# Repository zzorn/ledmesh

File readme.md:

Ledmesh
=======

Overview
--------

Mesh networked nodes controlling LED light strips, LED spotlights, sensors, and other things.

The network uses wireless radio modules to communicate between nodes.

Ledmesh can be used to create coherent led lighting effects in a space (e.g. light waves flowing around walls), 
as well as for controlling 12V lighting (e.g. led spotlights).

Ledmesh can also be used as an information radiator, connecting some nodes up to computers or suitable sensors, 
and sending out light waves to nearby nodes or doing light effect changes for the whole network on different events.

Ledmesh needs configuration after installation, to tell nodes their relative locations, sensors to use for activating different modes or sending waves, and so on.

Effects
-------

The main type of effect consist of nodes sending waves of light and color along light strips towards neighboring nodes, where the waves can carry on to other nodes.
Waves can have various intensity, hue/sat/lum (also negative), wavelength, travel distance/time, random noise, color gradients, and so on.  Multiple waves can travel along a strip in various directions
at the same time, the different waves are blended together.

Waves could leave the leds at zero after they pass, or they could leave them at some other intensity, which will be changed by the next wave.  (Or the base intensity might be based on the mode(s) the node is in?)

Waves can be used to create a lot of different effects (even global fade ins or outs).  If there are some ideas for effect types that are not possible to do with waves, those might be added later.

Single outputs, like led spotlights, could be treated like a led strip of length one (or some other length, if the spotlights are arranged in a row).

Node States
-----------

Nodes can have various states depending on their sensor readings and global or remote sensor readings received with communication from other nodes.
The state(s) a node is in determines what kind of effects it generates to attached led strips and other outputs.

A node need not be either in a state or not, it can also be partially in a state (e.g. a potentiometer could be used to place a node partially in a 'lit' state).

The degree a state is activated depends either directly or indirectly on one or more sensor inputs, with some multipliers.

Different states can also have different speeds or required activation that they activate or deactivate with (a kind of inertia), to provide some hysteresis and reduce quick flickering between states.

For more complicated behaviour, the activation degree of states in the current or neighboring nodes could be used as a sensor value to help determine the activation of a node (creating a neuron-like setup).

Modes
-----

Sometimes the general apperance of the whole network should be changed.  This could be done with a mode concept, where a mode enables states contained in it, and disables states contained within any previously active mode.
Some states might be independent of the mode.

One possibility is to allow multiple modes as once, although that might be more complications than necessary.

Modes could maybe change depending on signals (which would indicate some hierarchial state system might be better than a separate mode concept).

For example, during the evening a more orange toned lighting mode could be activated, there could be modes for work that needs a lot of light, for more muted lighting for general hanging around,
for some darker and slower night illumination, a party mode, and a few different looking general light modes.

Node types
----------

There are two different types of nodes:

* Led Node
  * Controls zero or more LED strips, LED lights, etc.  Also has two extra I/O pins.
  * Has locations for sensor modules such as PIR (motion detector) and sound.
  * Has builtin light level sensor.
  * Has location for a radio communication module.

* Remote Controller
  * Contains a character LCD screen and turn wheels (and possibly a color / color gradient preview LED) for configuring the network.  It allows:
     * Configuring the length of led strips connected to different nodes (needs to be done once after installation).  
     * Defining fixed signals for different nodes (e.g. height above floor, or x/y coordinate), which can be used in effects.
     * Defining the signals that different inputs on different nodes affect, and whether the signals are global or local to the node.
       Some inputs are pre-configured (e.g. light level sensors, etc), while others could be custom (e.g. door open microswitch, red alert/instant party button, etc).
     * Defining gradients.
     * Defining various named wave types.
     * Defining various wave generators (?).
     * Defining various node states
        * Connecting wave generators to the node state
        * Specifying the activation or deactivation effects of different signals (and state activations) from this node or neighboring nodes or global signals on this state.
        * Default lifetime of this state
        * Slowness / quickness of state change = change inertia
        * Whether this state should be available on all nodes, or only a selected subset (always non-active on other nodes)  [Is this needed?  Maybe not]
     * The default screen allows setting various selected global signals, and selecting the current mode(s).
  * Could also have a USB connection to computer, and some serial based protocol to provide updates to signal states, as well as communicate states from the Ledmess network.  The protocol could also contain commands for configuring LedMesh.
  * Might also contain support for bluetooth control (for control from android app)
  * Might support an ethernet connector as well.

Control and configuration application
-------------------------------------

To be written in Java, as that allows easy porting to both android and PC.

The software on the remote controller will probably be more limited, but it would be nice to be able to do all configuration from it if needed.

Builtin Signals
---------------

* Time of day
* Age of this state (0 = newborn, 100% = at the lifetime of the state).

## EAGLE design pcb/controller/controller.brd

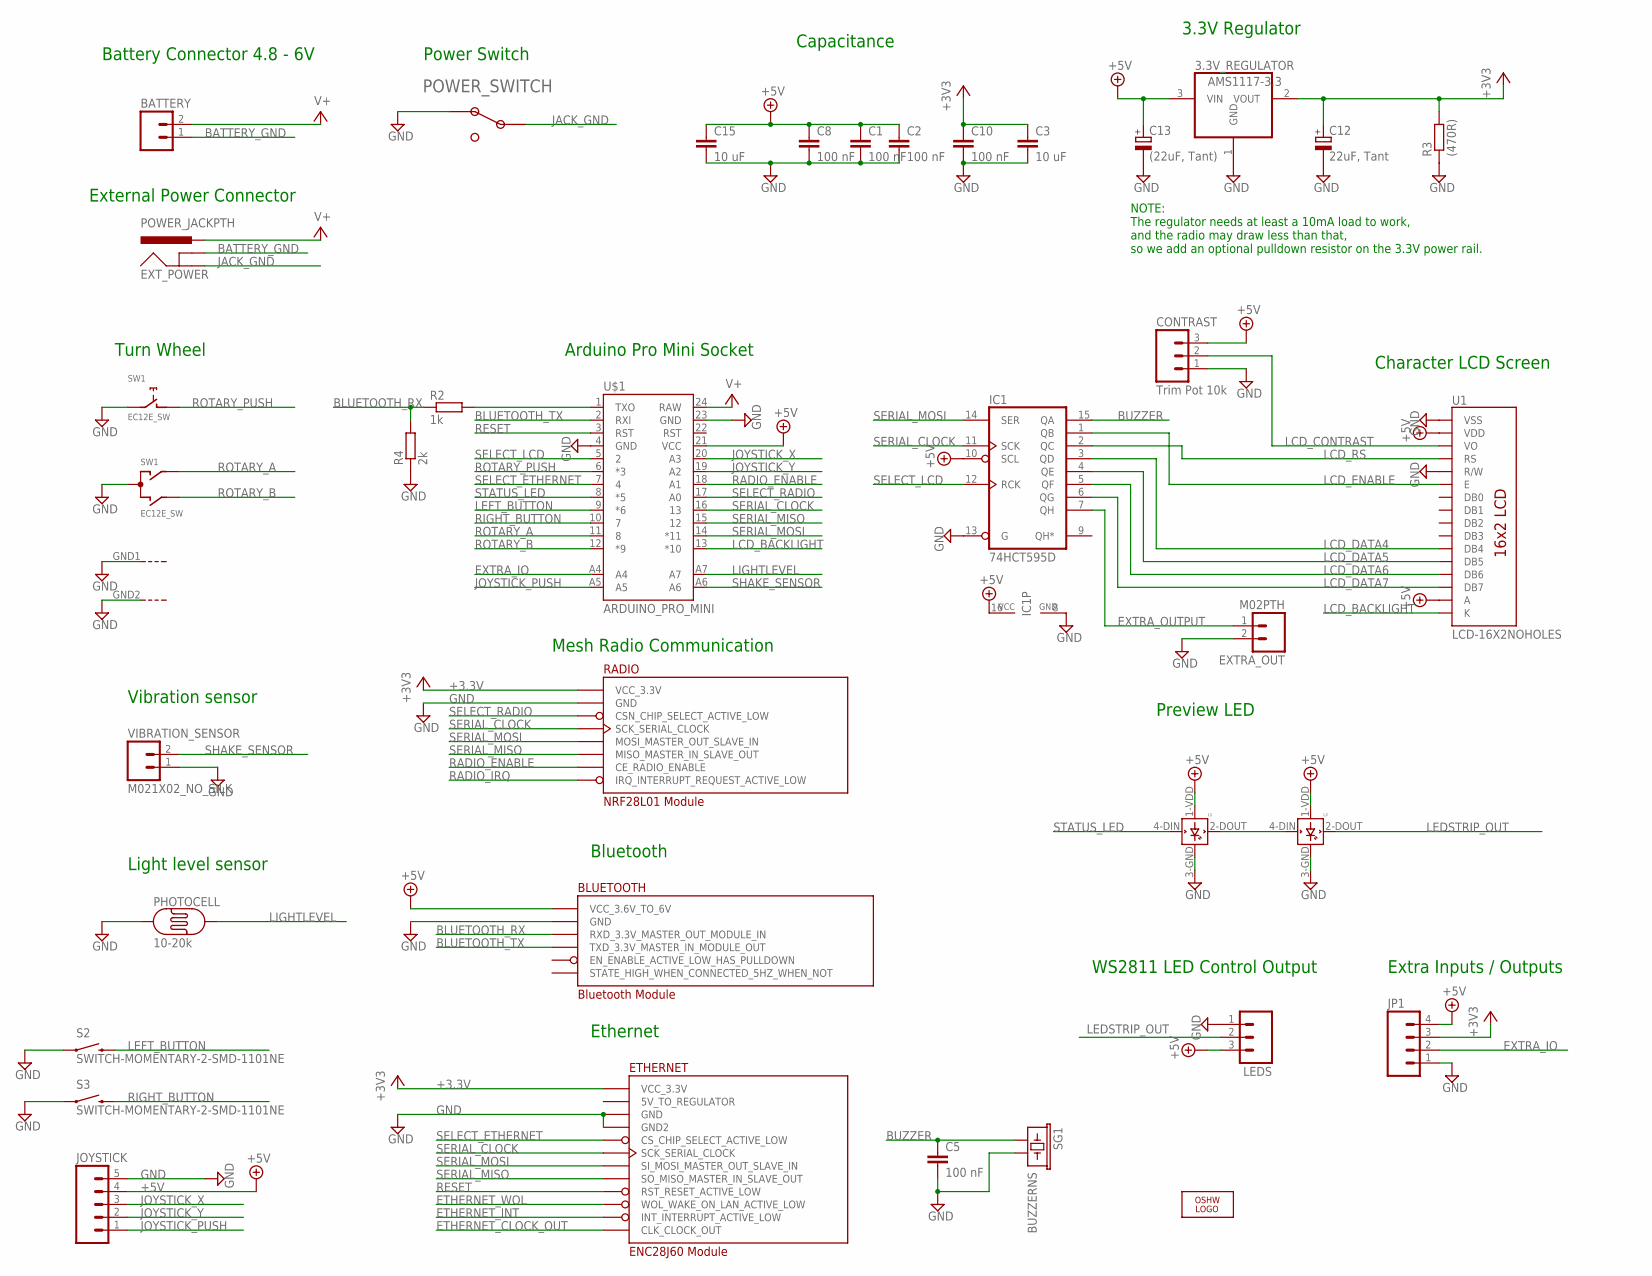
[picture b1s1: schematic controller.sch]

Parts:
3.3V_REGULATOR: AMS1117-3.3; SOT223
BATTERY: M02LOCK_LONGPADS; 1X02_LOCK_LONGPADS
BLUETOOTH: Bluetooth Module; BLUETOOTH_MODULE
C1, C2, C5, C8, C10: 100 nF; C0805
C3, C15: 10 uF; C0805K
C12: 22uF, Tant; SMC_A
C13: (22uF, Tant); SMC_A
CONTRAST: Trim Pot 10k; 1X03_NO_SILK
ETHERNET: ENC28J60 Module; ETHERNET_ENC28J60_MODULE
EXTRA_OUT: M02PTH; 1X02
EXT_POWER: POWER_JACKPTH; POWER_JACK_PTH
IC1: 74HCT595D; SO16
JOYSTICK: M05NO_SILK; 1X05_NO_SILK
JP1: M041X04_NO_SILK; 1X04_NO_SILK
L1, L2: WS2812B
LEDS: M03PTH; 1X03
LOGO3: LOGO-OSHW-8MILX0100-NT; OSHW_8X100_NOTEXT
PHOTOCELL: 10-20k; PHOTOCELL
POWER_SWITCH: KNC1-101-2P
R2: 1k; M0805
R3: (470R); M0805
R4: 2k; M0805
RADIO: NRF28L01 Module; NRF24L01_MODULE
S2, S3: SWITCH-MOMENTARY-2-SMD-1101NE; TACTILE-SWITCH-1101NE
SG1: BUZZERNS; BUZZER-12MM-NS
SW1: EC12E_SW; ALPS_EC12E_SW
U1: LCD-16X2NOHOLES; LCD-16X2_NOHOLES
U$1: ARDUINO_PRO_MINI
VIBRATION_SENSOR: M021X02_NO_SILK; 1X02_NO_SILK

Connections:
+3.3V: 3.3V_REGULATOR.2 (VOUT), C3.1, C10.1, C12.+, ETHERNET.P$2 (VCC_3.3V), JP1.3, R3.2, RADIO.P$2 (VCC_3.3V)
+5V: 3.3V_REGULATOR.3 (VIN), BLUETOOTH.P$5 (VCC_3.6V_TO_6V), C1.1, C2.1, C8.1, C13.+, C15.1, CONTRAST.3, IC1.10 (SCL), IC1.16 (VCC), JOYSTICK.4, JP1.4, L1.1-VDD (VDD), L2.1-VDD (VDD), LEDS.3, U1.2 (VDD), U1.15 (A), U$1.21 (VCC)
BATTERY_GND: BATTERY.1, EXT_POWER.GNDBREAK
BLUETOOTH_RX: BLUETOOTH.P$2 (RXD_3.3V_MASTER_OUT_MODULE_IN), R2.1, R4.2
BLUETOOTH_TX: BLUETOOTH.P$3 (TXD_3.3V_MASTER_IN_MODULE_OUT), U$1.2 (RXI)
BUZZER: C5.1, IC1.15 (QA), SG1.+ (1)
ETHERNET_CLOCK_OUT: ETHERNET.P$9 (CLK_CLOCK_OUT)
ETHERNET_INT: ETHERNET.P$10 (INT_INTERRUPT_ACTIVE_LOW)
ETHERNET_WOL: ETHERNET.P$7 (WOL_WAKE_ON_LAN_ACTIVE_LOW)
EXTRA_IO: JP1.2, U$1.A4
EXTRA_OUTPUT: EXTRA_OUT.1, IC1.7 (QH)
GND: 3.3V_REGULATOR.1 (GND), BLUETOOTH.P$4 (GND), C1.2, C2.2, C3.2, C5.2, C8.2, C10.2, C12.-, C13.-, C15.2, CONTRAST.1, ETHERNET.P$1 (GND), ETHERNET.P$11 (GND2), EXTRA_OUT.2, IC1.8 (GND), IC1.13 (G), JOYSTICK.5, JP1.1, L1.3-GND (GND), L2.3-GND (GND), LEDS.1, PHOTOCELL.1, POWER_SWITCH.P$1, R3.1, R4.1, RADIO.P$1 (GND), S2.P$1 (1), S3.P$1 (1), SG1.- (2), SW1.C, SW1.E (2), SW1.GND1 (G), SW1.GND2 (G), U1.1 (VSS), U1.5 (R/W), U$1.4 (GND), U$1.23 (GND), VIBRATION_SENSOR.1
JACK_GND: EXT_POWER.GND, POWER_SWITCH.P$2
JOYSTICK_PUSH: JOYSTICK.1, U$1.A5
JOYSTICK_X: JOYSTICK.3, U$1.20 (A3)
JOYSTICK_Y: JOYSTICK.2, U$1.19 (A2)
LCD_BACKLIGHT: U1.16 (K), U$1.13 (*10)
LCD_CONTRAST: CONTRAST.2, U1.3 (VO)
LCD_DATA4: IC1.3 (QD), U1.11 (DB4)
LCD_DATA5: IC1.4 (QE), U1.12 (DB5)
LCD_DATA6: IC1.5 (QF), U1.13 (DB6)
LCD_DATA7: IC1.6 (QG), U1.14 (DB7)
LCD_ENABLE: IC1.1 (QB), U1.6 (E)
LCD_RS: IC1.2 (QC), U1.4 (RS)
LEDSTRIP_OUT: L2.2-DOUT (DOUT), LEDS.2
LEFT_BUTTON: S2.P$2 (2), U$1.9 (*6)
LIGHTLEVEL: PHOTOCELL.2, U$1.A7
unnamed: R2.2, U$1.1 (TXO)
RADIO_ENABLE: RADIO.P$3 (CE_RADIO_ENABLE), U$1.18 (A1)
RADIO_IRQ: RADIO.P$8 (IRQ_INTERRUPT_REQUEST_ACTIVE_LOW)
RESET: ETHERNET.P$4 (RST_RESET_ACTIVE_LOW), U$1.3 (RST)
RIGHT_BUTTON: S3.P$2 (2), U$1.10 (7)
ROTARY_A: SW1.A, U$1.11 (8)
ROTARY_B: SW1.B, U$1.12 (*9)
ROTARY_PUSH: SW1.D (1), U$1.6 (*3)
SELECT_ETHERNET: ETHERNET.P$3 (CS_CHIP_SELECT_ACTIVE_LOW), U$1.7 (4)
SELECT_LCD: IC1.12 (RCK), U$1.5 (2)
SELECT_RADIO: RADIO.P$4 (CSN_CHIP_SELECT_ACTIVE_LOW), U$1.17 (A0)
SERIAL_CLOCK: ETHERNET.P$6 (SCK_SERIAL_CLOCK), IC1.11 (SCK), RADIO.P$5 (SCK_SERIAL_CLOCK), U$1.16 (13)
SERIAL_MISO: ETHERNET.P$8 (SO_MISO_MASTER_IN_SLAVE_OUT), RADIO.P$7 (MISO_MASTER_IN_SLAVE_OUT), U$1.15 (12)
SERIAL_MOSI: ETHERNET.P$5 (SI_MOSI_MASTER_OUT_SLAVE_IN), IC1.14 (SER), RADIO.P$6 (MOSI_MASTER_OUT_SLAVE_IN), U$1.14 (*11)
SHAKE_SENSOR: U$1.A6, VIBRATION_SENSOR.2
STATUS_LED: L1.4-DIN (DIN), U$1.8 (*5)
STATUS_LED2: L1.2-DOUT (DOUT), L2.4-DIN (DIN)
V+: BATTERY.2, EXT_POWER.PWR, U$1.24 (RAW)

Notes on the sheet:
Arduino Pro Mini Socket
Capacitance
Light level sensor
Extra Inputs / Outputs
Battery Connector 4.8 - 6V
Mesh Radio Communication
3.3V Regulator
NOTE: The regulator needs at least a 10mA load to work, and the radio may draw less than that, so we add an optional pulldown resistor on the 3.3V power rail.
Preview LED
Vibration sensor
Turn Wheel
Character LCD Screen
WS2811 LED Control Output
Bluetooth
Ethernet
External Power Connector
Power Switch

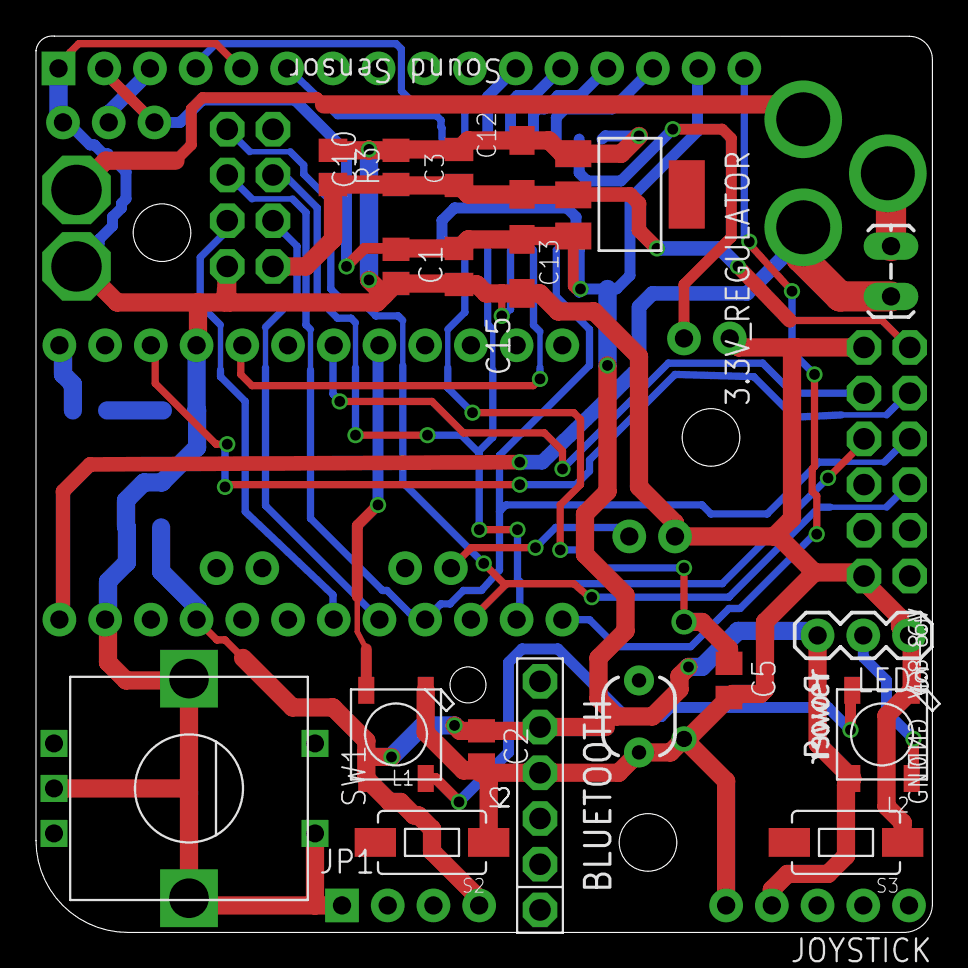
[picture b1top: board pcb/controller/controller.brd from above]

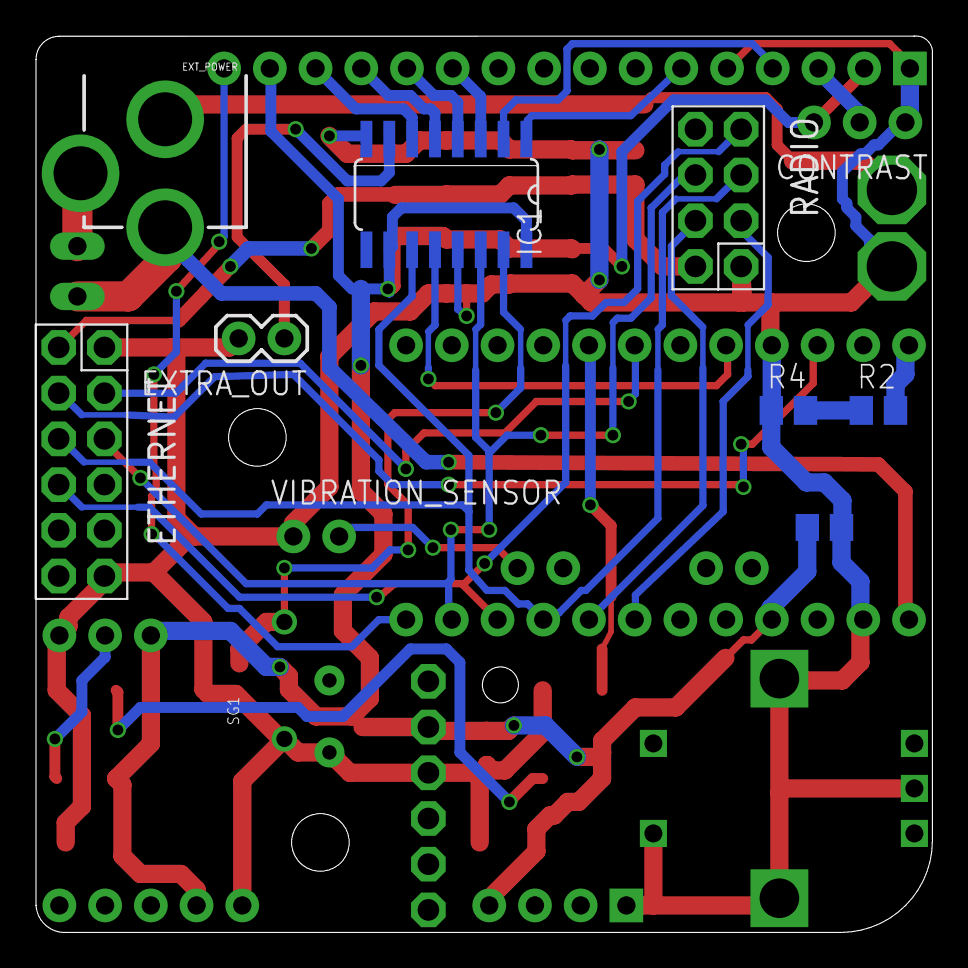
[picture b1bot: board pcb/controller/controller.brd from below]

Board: 2 copper layers, 49.8 x 49.8 mm, 36 parts (12 on the bottom side), 41 nets.

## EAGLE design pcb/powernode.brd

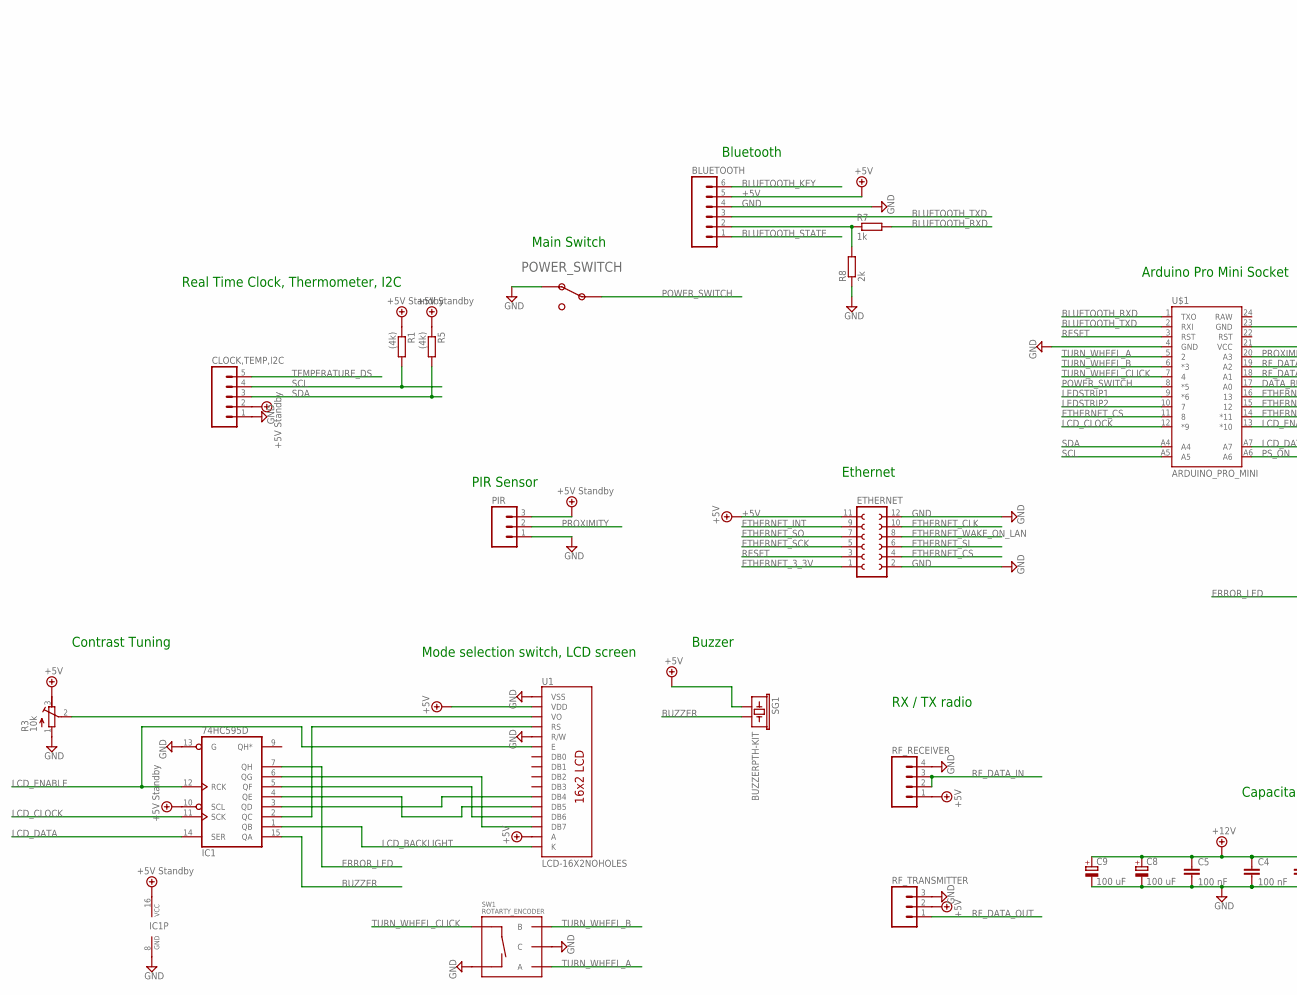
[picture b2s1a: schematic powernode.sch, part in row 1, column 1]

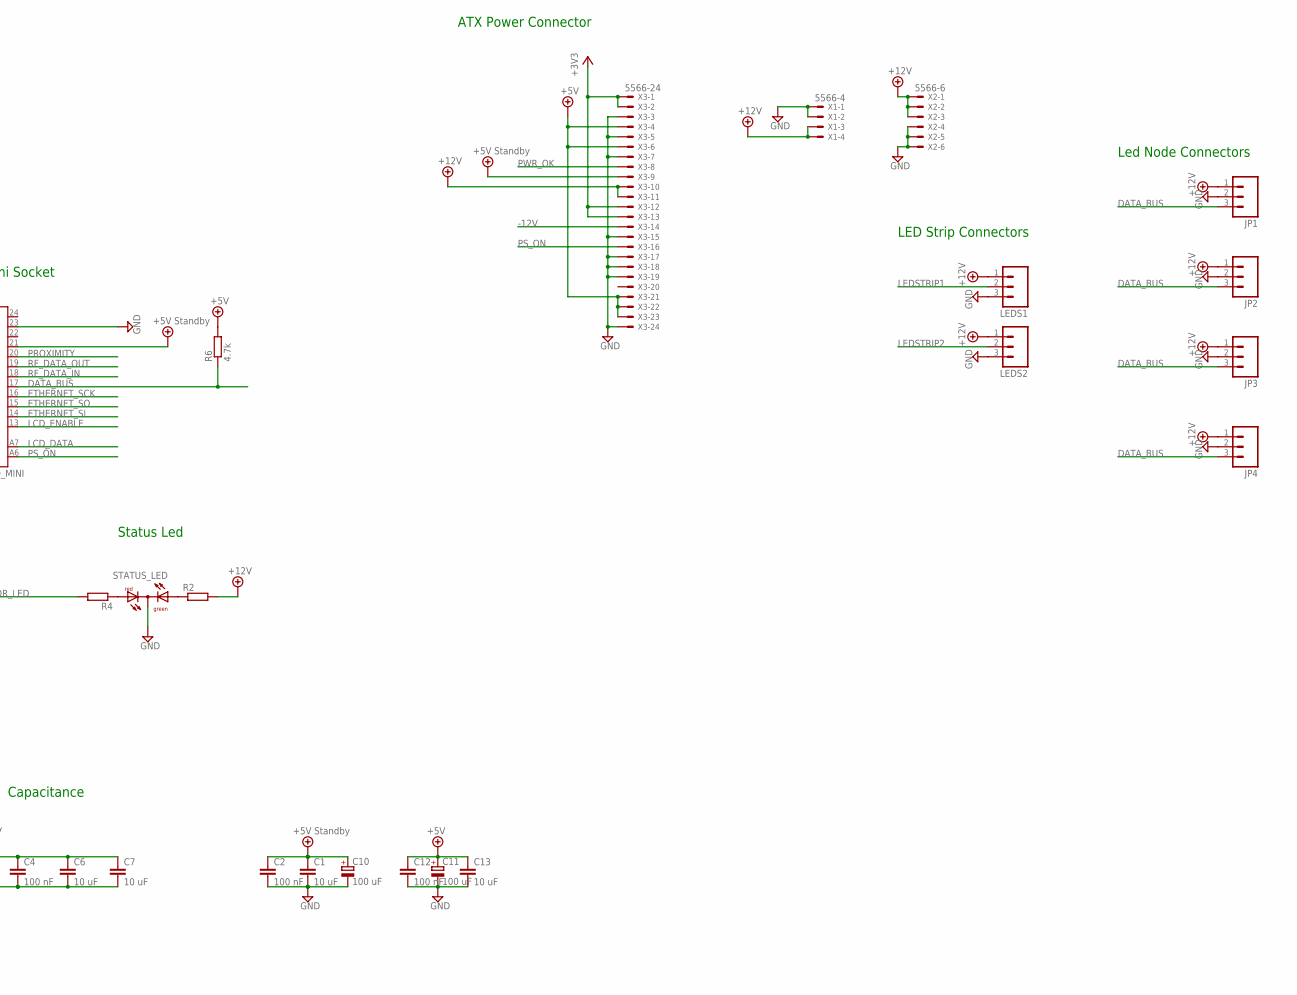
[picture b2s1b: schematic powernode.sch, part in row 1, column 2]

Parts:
BLUETOOTH: M06NO_SILK; 1X06_NO_SILK
C1, C6, C7, C13: 10 uF; C1206
C2, C4, C5, C12: 100 nF; C0805
C8, C9, C10, C11: 100 uF; E2,5-6
CLOCK,TEMP,I2C: M05PTH; 1X05
ETHERNET: FE06-2
IC1: 74HC595D; SO16
JP1, JP2, JP3, JP4: M03-SCREW-5MM; SCREWTERMINAL-5MM-3
LEDS1, LEDS2: M03LONGPADS; 1X03_LONGPADS
PIR: M031X03_NO_SILK; 1X03_NO_SILK
POWER_SWITCH: KNC1-101-2P
R1, R5: (4k); R0805
R2, R4: R-EU_R0805; R0805
R3: 10k; RTRIM3296W
R6: 4.7k; R0805
R7: 1k; R0805
R8: 2k; R0805
RF_RECEIVER: M041X04_NO_SILK; 1X04_NO_SILK
RF_TRANSMITTER: M031X03_NO_SILK; 1X03_NO_SILK
SG1: BUZZERPTH-KIT; BUZZER-12MM-KIT
STATUS_LED: DUOLED-RG-C; DUOLED-C-5MM
SW1: ROTARTY_ENCODER; ROTARY_ENC_PLAIN
U1: LCD-16X2NOHOLES; LCD-16X2_NOHOLES
U$1: ARDUINO_PRO_MINI
X1: 5566-4
X2: 5566-6
X3: 5566-24

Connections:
+3V3: X3.1, X3.2, X3.12, X3.13
+5V: BLUETOOTH.5, C11.+, C12.1, C13.1, ETHERNET.11, R3.3 (A), R6.2, RF_RECEIVER.1, RF_TRANSMITTER.2, SG1.+ (1), U1.2 (VDD), U1.15 (A), X3.4, X3.6, X3.21, X3.22, X3.23
+5V/2: C1.1, C2.1, C10.+, CLOCK,TEMP,I2C.2, IC1.10 (SCL), IC1.16 (VCC), PIR.3, R1.1, R5.1, U$1.21 (VCC), X3.9
+12V: C4.1, C5.1, C6.1, C7.1, C8.+, C9.+, JP1.1, JP2.1, JP3.1, JP4.1, LEDS1.1, LEDS2.1, R2.2, X1.3, X1.4, X2.1, X2.2, X2.3, X3.10, X3.11
-12V: X3.14
BLUETOOTH_KEY: BLUETOOTH.6
BLUETOOTH_RXD: R7.2, U$1.1 (TXO)
BLUETOOTH_STATE: BLUETOOTH.1
BLUETOOTH_TXD: BLUETOOTH.3, U$1.2 (RXI)
BUZZER: IC1.15 (QA), SG1.- (2)
DATA_BUS: JP1.3, JP2.3, JP3.3, JP4.3, R6.1, U$1.17 (A0)
ERROR_LED: IC1.7 (QH), R4.2
ETHERNET_3_3V: ETHERNET.1
ETHERNET_CLK: ETHERNET.10
ETHERNET_CS: ETHERNET.4, U$1.11 (8)
ETHERNET_INT: ETHERNET.9
ETHERNET_SCK: ETHERNET.5, U$1.16 (13)
ETHERNET_SI: ETHERNET.6, U$1.14 (*11)
ETHERNET_SO: ETHERNET.7, U$1.15 (12)
ETHERNET_WAKE_ON_LAN: ETHERNET.8
GND: BLUETOOTH.4, C1.2, C2.2, C4.2, C5.2, C6.2, C7.2, C8.-, C9.-, C10.-, C11.-, C12.2, C13.2, CLOCK,TEMP,I2C.1, ETHERNET.2, ETHERNET.12, IC1.8 (GND), IC1.13 (G), JP1.2, JP2.2, JP3.2, JP4.2, LEDS1.3, LEDS2.3, PIR.1, POWER_SWITCH.P$1, R3.1 (E), R8.1, RF_RECEIVER.4, RF_TRANSMITTER.3, STATUS_LED.C, SW1.C, SW1.SW-, U1.1 (VSS), U1.5 (R/W), U$1.4 (GND), U$1.23 (GND), X1.1, X1.2, X2.4, X2.5, X2.6, X3.3, X3.5, X3.7, X3.15, X3.17, X3.18, X3.19, X3.24
LCD_BACKLIGHT: IC1.1 (QB), U1.16 (K)
LCD_CLOCK: IC1.11 (SCK), U$1.12 (*9)
LCD_DATA: IC1.14 (SER), U$1.A7
LCD_ENABLE: IC1.12 (RCK), U1.6 (E), U$1.13 (*10)
LEDSTRIP1: LEDS1.2, U$1.9 (*6)
LEDSTRIP2: LEDS2.2, U$1.10 (7)
unnamed: IC1.3 (QD), U1.11 (DB4)
unnamed: IC1.2 (QC), U1.4 (RS)
unnamed: R2.1, STATUS_LED.AX (AG)
unnamed: IC1.4 (QE), U1.12 (DB5)
unnamed: IC1.5 (QF), U1.13 (DB6)
unnamed: IC1.6 (QG), U1.14 (DB7)
unnamed: R4.1, STATUS_LED.AR
unnamed: BLUETOOTH.2, R7.1, R8.2
POWER_SWITCH: POWER_SWITCH.P$2, U$1.8 (*5)
PROXIMITY: PIR.2, U$1.20 (A3)
PS_ON: U$1.A6, X3.16
PWR_OK: X3.8
RESET: ETHERNET.3, U$1.3 (RST)
RF_DATA_IN: RF_RECEIVER.2, RF_RECEIVER.3, U$1.18 (A1)
RF_DATA_OUT: RF_TRANSMITTER.1, U$1.19 (A2)
SCL: CLOCK,TEMP,I2C.4, R1.2, U$1.A5
SDA: CLOCK,TEMP,I2C.3, R5.2, U$1.A4
TEMPERATURE_DS: CLOCK,TEMP,I2C.5
TURN_WHEEL_A: SW1.A, U$1.5 (2)
TURN_WHEEL_B: SW1.B, U$1.6 (*3)
TURN_WHEEL_CLICK: SW1.SW+, U$1.7 (4)

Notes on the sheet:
ATX Power Connector
Arduino Pro Mini Socket
Capacitance
LED Strip Connectors
RX / TX radio
Bluetooth
Buzzer
Status Led
Main Switch
PIR Sensor
Led Node Connectors
Mode selection switch, LCD screen
Ethernet
Contrast Tuning
Real Time Clock, Thermometer, I2C

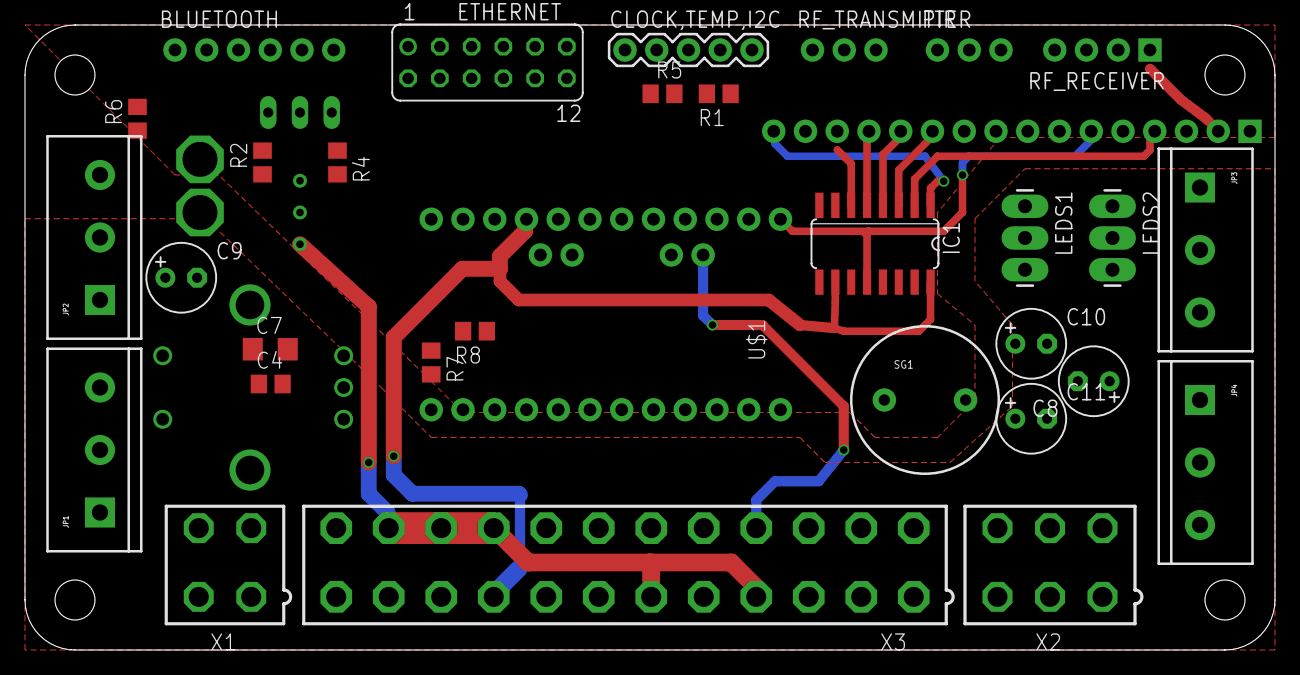
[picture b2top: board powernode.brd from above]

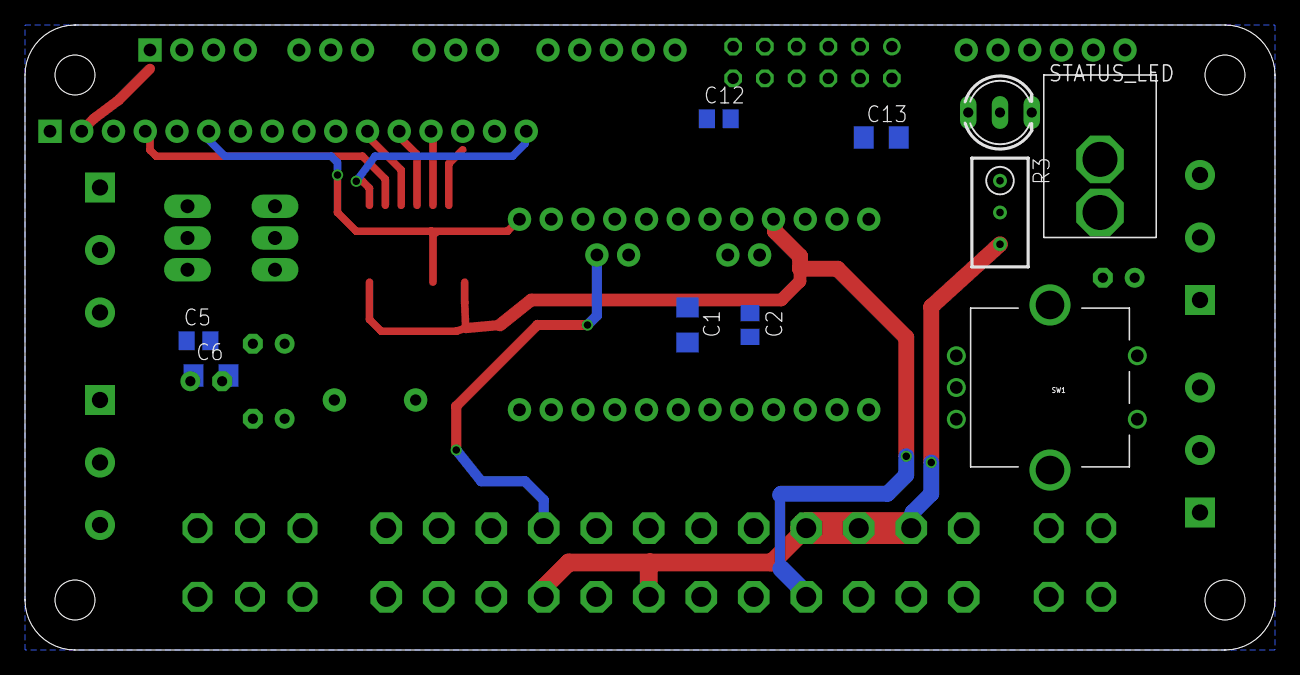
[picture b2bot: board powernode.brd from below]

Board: 2 copper layers, 100.0 x 50.0 mm, 42 parts (11 on the bottom side), 39 nets.

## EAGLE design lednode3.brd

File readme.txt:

Controller for several channels of RGB LED lights, e.g. LED strips.

The aim is to include both an arduino program for controlling it, as well as shematics for the controller circuit.

GPL licensed.

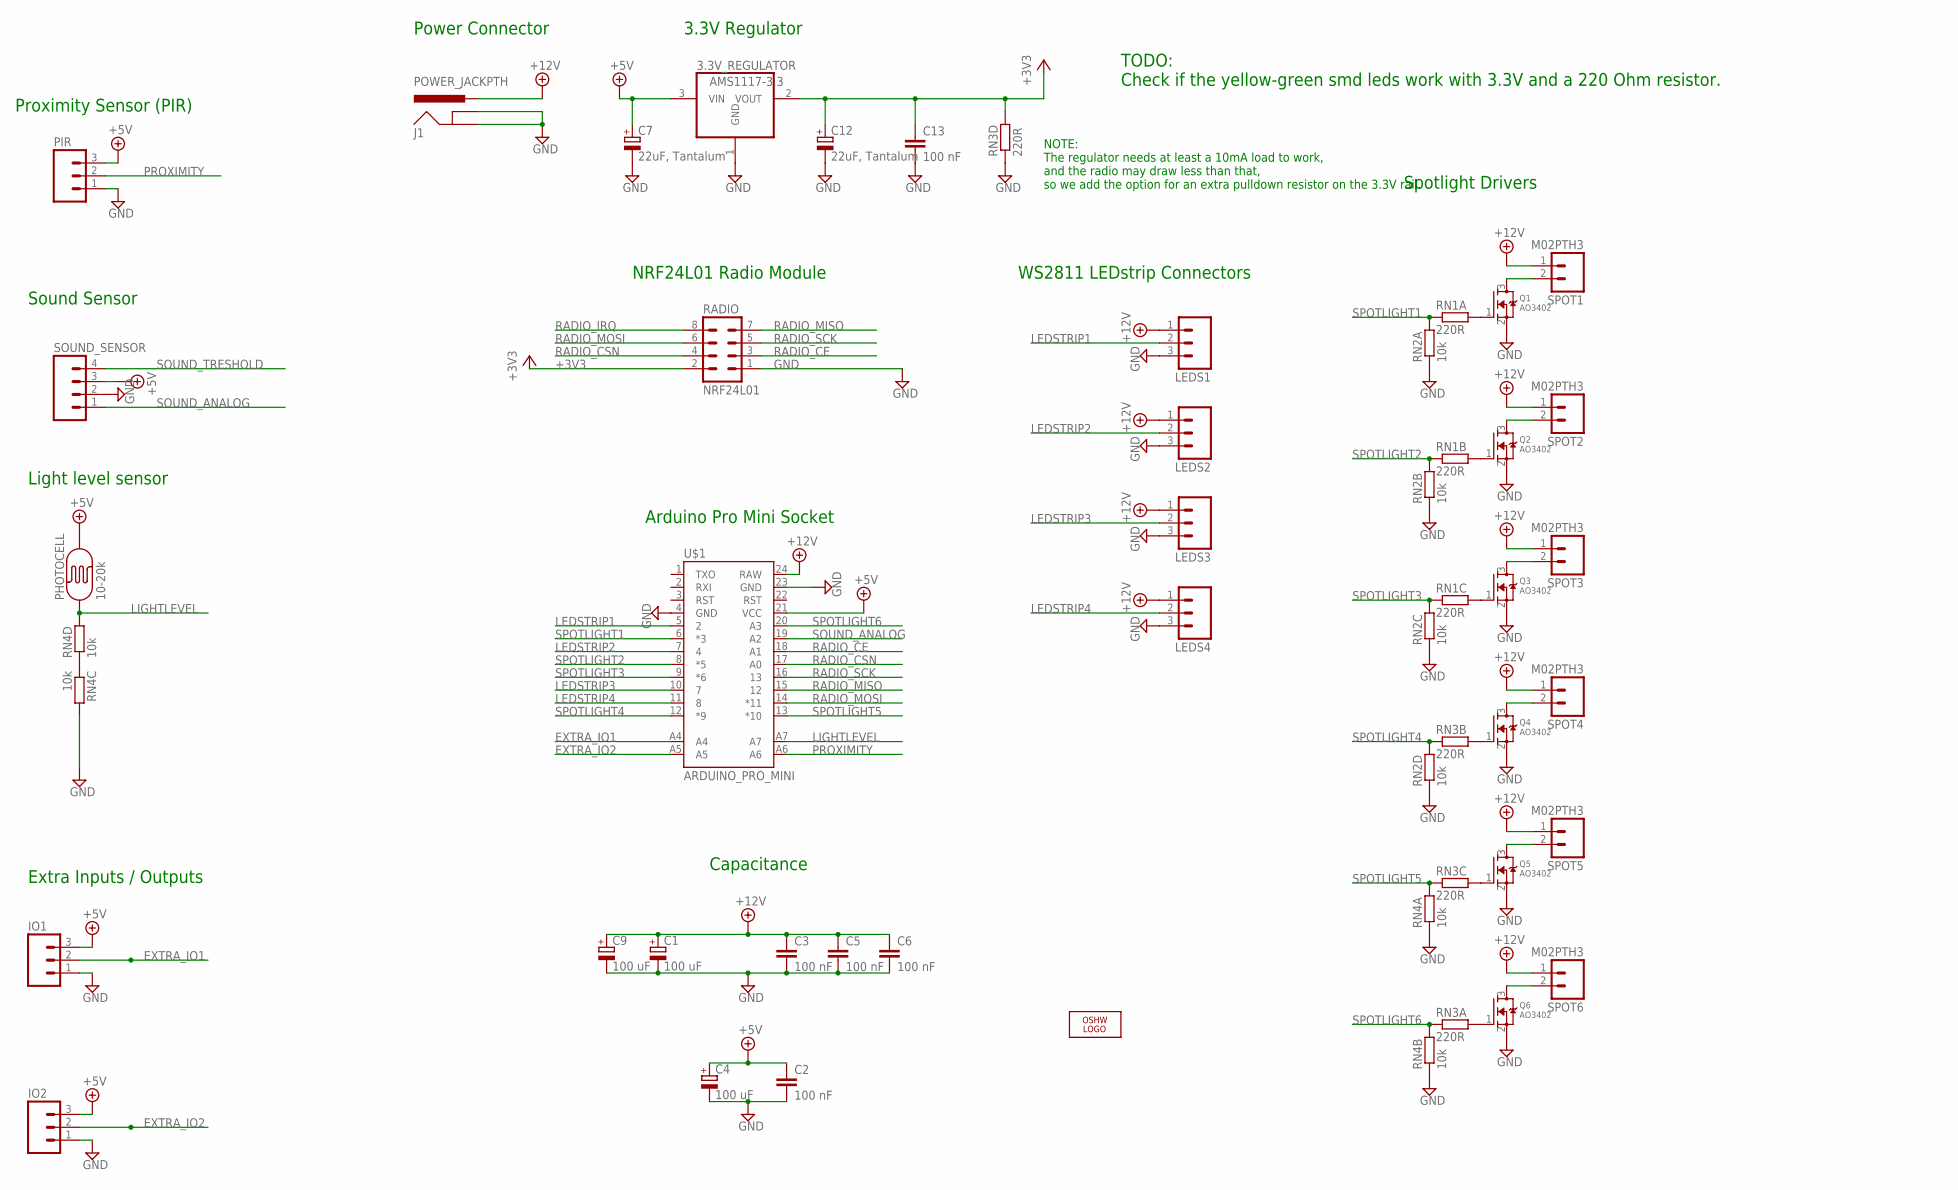
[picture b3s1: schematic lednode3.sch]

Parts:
3.3V_REGULATOR: AMS1117-3.3; SOT223
C1, C4, C9: 100 uF; E2,5-6
C2, C3, C5, C6, C13: 100 nF; C0805
C7, C12: 22uF, Tantalum; SMC_A
IO1, IO2: M03PTH; 1X03
J1: POWER_JACKPTH; POWER_JACK_PTH
LEDS1, LEDS2, LEDS3, LEDS4: M03LONGPADS; 1X03_LONGPADS
LOGO3: LOGO-OSHW-8MILX0100-NT; OSHW_8X100_NOTEXT
PHOTOCELL: 10-20k; PHOTOCELL
PIR: M03PTH; 1X03
Q1, Q2, Q3, Q4, Q5, Q6: AO3402; SOT23-W
RADIO: NRF24L01; MA04-2
RN1, RN3: 220R; RN8P-4R-CRA06S
RN2, RN4: 10k; RN8P-4R-CRA06S
SOUND_SENSOR: M041X04_NO_SILK; 1X04_NO_SILK
SPOT1, SPOT2, SPOT3, SPOT4, SPOT5, SPOT6: M02PTH3; 1X02_LONGPADS
U$1: ARDUINO_PRO_MINI

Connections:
+3V3: 3.3V_REGULATOR.2 (VOUT), C12.+, C13.1, RADIO.2, RN3.5 (2)
+5V: 3.3V_REGULATOR.3 (VIN), C2.1, C4.+, C7.+, IO1.3, IO2.3, PHOTOCELL.2, PIR.3, SOUND_SENSOR.3, U$1.21 (VCC)
+12V: C1.+, C3.1, C5.1, C6.1, C9.+, J1.PWR, LEDS1.1, LEDS2.1, LEDS3.1, LEDS4.1, SPOT1.1, SPOT2.1, SPOT3.1, SPOT4.1, SPOT5.1, SPOT6.1, U$1.24 (RAW)
EXTRA_IO1: IO1.2, U$1.A4
EXTRA_IO2: IO2.2, U$1.A5
GND: 3.3V_REGULATOR.1 (GND), C1.-, C2.2, C3.2, C4.-, C5.2, C6.2, C7.-, C9.-, C12.-, C13.2, IO1.1, IO2.1, J1.GND, J1.GNDBREAK, LEDS1.3, LEDS2.3, LEDS3.3, LEDS4.3, PIR.1, Q1.2 (S), Q2.2 (S), Q3.2 (S), Q4.2 (S), Q5.2 (S), Q6.2 (S), RADIO.1, RN2.1, RN2.2 (1), RN2.3 (1), RN2.4 (1), RN3.4 (1), RN4.1, RN4.2 (1), RN4.6 (2), SOUND_SENSOR.2, U$1.4 (GND), U$1.23 (GND)
LEDSTRIP1: LEDS1.2, U$1.5 (2)
LEDSTRIP2: LEDS2.2, U$1.7 (4)
LEDSTRIP3: LEDS3.2, U$1.10 (7)
LEDSTRIP4: LEDS4.2, U$1.11 (8)
LIGHTLEVEL: PHOTOCELL.1, RN4.5 (2), U$1.A7
unnamed: Q5.3 (D), SPOT5.2
unnamed: Q1.3 (D), SPOT1.2
unnamed: Q2.3 (D), SPOT2.2
unnamed: Q4.3 (D), SPOT4.2
unnamed: Q3.3 (D), SPOT3.2
unnamed: Q1.1 (G), RN1.8 (2)
unnamed: Q2.1 (G), RN1.7 (2)
unnamed: Q4.1 (G), RN3.7 (2)
unnamed: Q3.1 (G), RN1.6 (2)
unnamed: Q5.1 (G), RN3.6 (2)
unnamed: Q6.3 (D), SPOT6.2
unnamed: RN4.3 (1), RN4.4 (1)
unnamed: Q6.1 (G), RN3.8 (2)
PROXIMITY: PIR.2, U$1.A6
RADIO_CE: RADIO.3, U$1.18 (A1)
RADIO_CSN: RADIO.4, U$1.17 (A0)
RADIO_IRQ: RADIO.8
RADIO_MISO: RADIO.7, U$1.15 (12)
RADIO_MOSI: RADIO.6, U$1.14 (*11)
RADIO_SCK: RADIO.5, U$1.16 (13)
SOUND_ANALOG: SOUND_SENSOR.1, U$1.19 (A2)
SOUND_TRESHOLD: SOUND_SENSOR.4
SPOTLIGHT1: RN1.1, RN2.8 (2), U$1.6 (*3)
SPOTLIGHT2: RN1.2 (1), RN2.7 (2), U$1.8 (*5)
SPOTLIGHT3: RN1.3 (1), RN2.6 (2), U$1.9 (*6)
SPOTLIGHT4: RN2.5 (2), RN3.2 (1), U$1.12 (*9)
SPOTLIGHT5: RN3.3 (1), RN4.8 (2), U$1.13 (*10)
SPOTLIGHT6: RN3.1, RN4.7 (2), U$1.20 (A3)

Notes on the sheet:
Arduino Pro Mini Socket
Capacitance
WS2811 LEDstrip Connectors
Light level sensor
Proximity Sensor (PIR)
Extra Inputs / Outputs
Power Connector
Spotlight Drivers
Sound Sensor
NRF24L01 Radio Module
3.3V Regulator
NOTE: The regulator needs at least a 10mA load to work, and the radio may draw less than that, so we add the option for an extra pulldown resistor on the 3.3V rail.
TODO: Check if the yellow-green smd leds work with 3.3V and a 220 Ohm resistor.

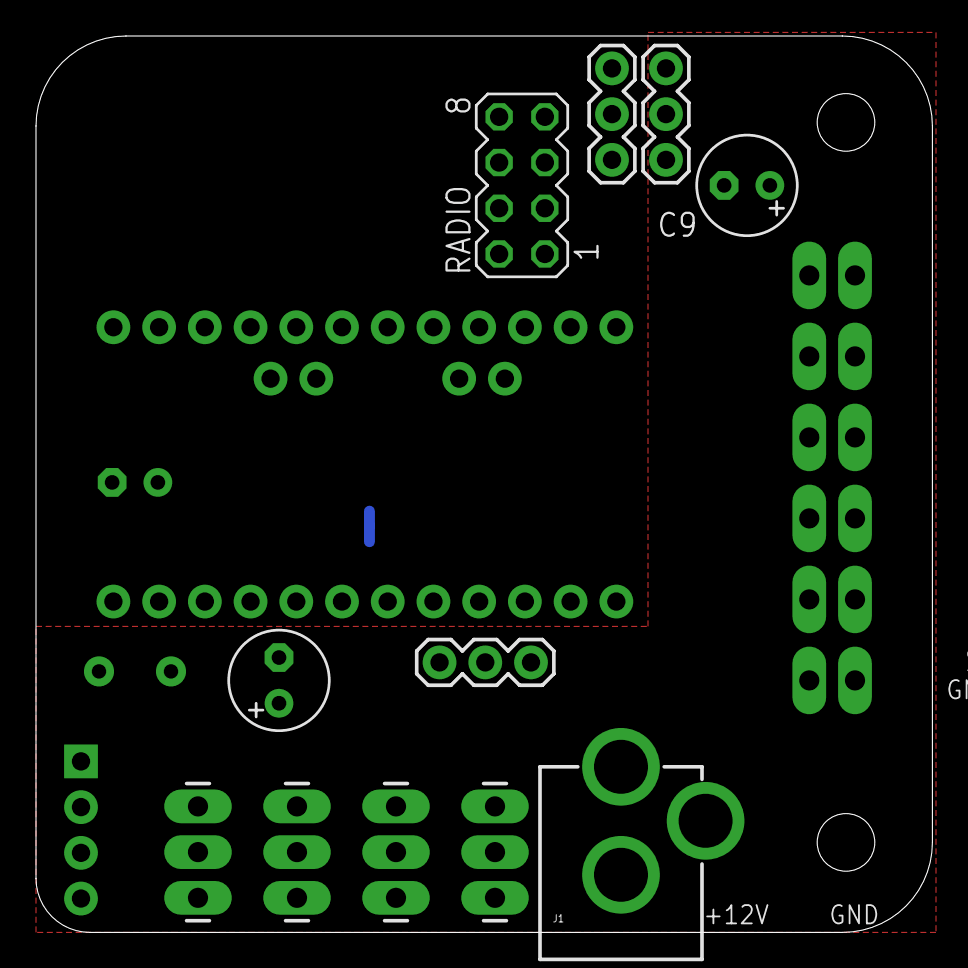
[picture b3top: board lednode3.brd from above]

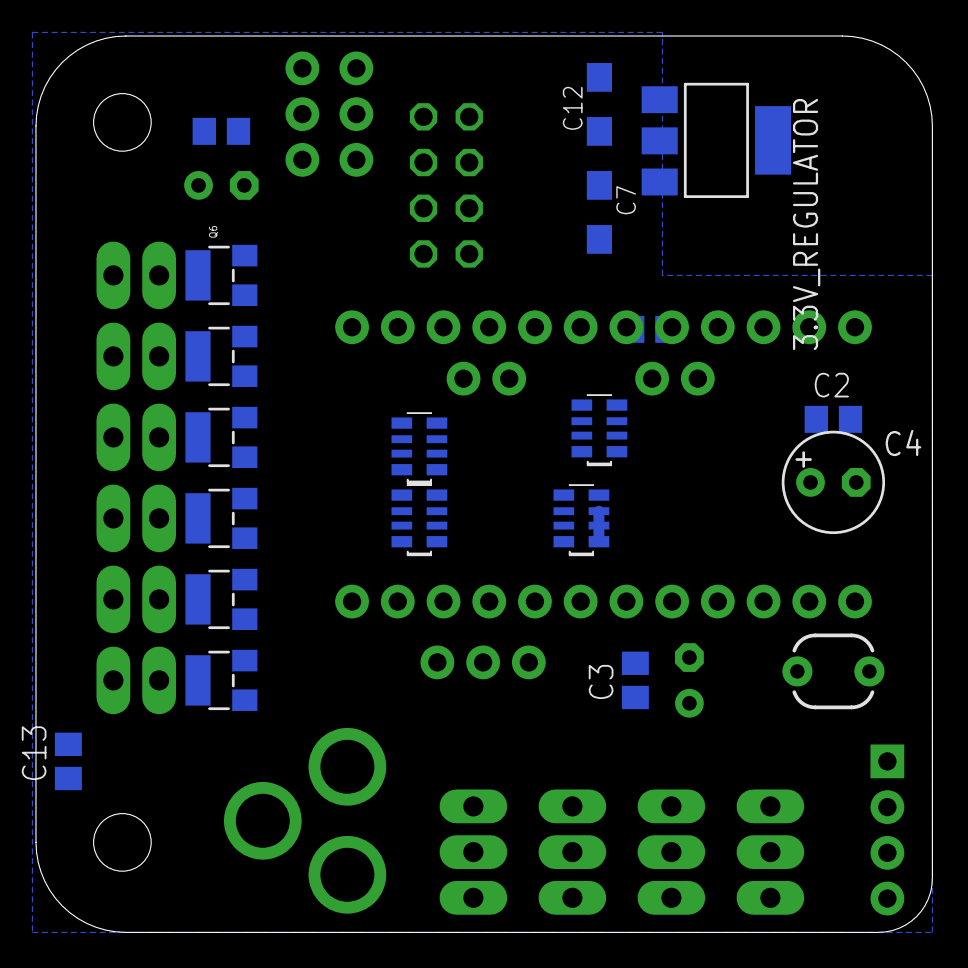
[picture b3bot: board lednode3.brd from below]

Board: 2 copper layers, 49.8 x 49.8 mm, 40 parts (21 on the bottom side), 37 nets.

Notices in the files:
parts and their libraries:
SparkFun-Connectors: Licensing: Creative Commons ShareAlike 4.0 International - https://creativecommons.org/licenses/by-sa/4.0
SparkFun: Licensing: CC v3.0 Share-Alike You are welcome to use this library for commercial purposes.
